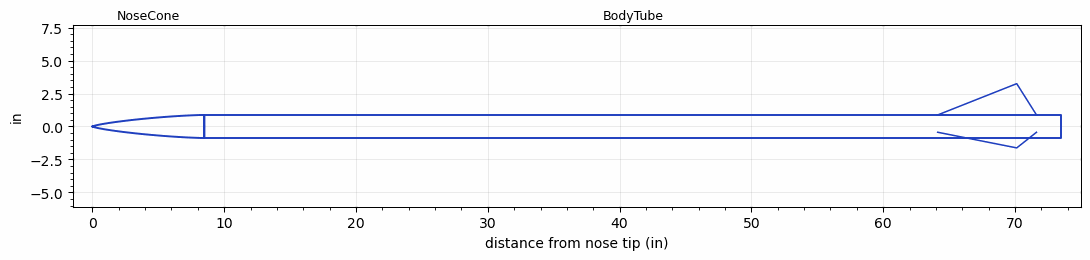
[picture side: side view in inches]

<RASAeroDocument>
 <FileVersion>2</FileVersion>
 <RocketDesign>
  <NoseCone>
   <Length>8.5</Length>
   <Diameter>1.75</Diameter>
   <Shape>Von Karman Ogive</Shape>
   <Location>0</Location>
  </NoseCone>
  <BodyTube>
   <Length>65</Length>
   <Diameter>1.75</Diameter>
   <RailGuideDiameter>0.375</RailGuideDiameter>
   <RailGuideHeight>0.3438</RailGuideHeight>
   <Location>8.5</Location>
   <Fin>
    <Count>3</Count>
    <Chord>7.5</Chord>
    <Span>2.375</Span>
    <SweepDistance>6</SweepDistance>
    <TipChord>0</TipChord>
    <Thickness>0.125</Thickness>
    <Location>9.370003</Location>
    <AirfoilSection>Rounded</AirfoilSection>
   </Fin>
  </BodyTube>
  <Surface>Smooth (Zero Roughness)</Surface>
  <ModifiedBarrowman>False</ModifiedBarrowman>
  <Turbulence>False</Turbulence>
  <UseBooster1>False</UseBooster1>
  <UseBooster2>False</UseBooster2>
  <Comments>Raven - Dave Rose
LDRS-26
Jean Dry Lake

Barometric Altimeter
Altitude = 8815 ft

RASAero II Prediction = 9332 ft
Error = 5.87%
</Comments>
 </RocketDesign>
 <LaunchSite>
  <Altitude>2750</Altitude>
  <Pressure>0</Pressure>
  <RodAngle>0</RodAngle>
  <RodLength>10</RodLength>
  <Temperature>100</Temperature>
  <WindSpeed>0</WindSpeed>
 </LaunchSite>
 <Recovery>
  <Altitude1>1000</Altitude1>
  <Altitude2>1000</Altitude2>
  <DeviceType1>None</DeviceType1>
  <DeviceType2>None</DeviceType2>
  <Event1>False</Event1>
  <Event2>False</Event2>
  <Size1>1</Size1>
  <Size2>1</Size2>
  <EventType1>None</EventType1>
  <EventType2>None</EventType2>
  <CD1>1.33</CD1>
  <CD2>1.33</CD2>
 </Recovery>
 <SimulationList>
  <Simulation>
   <SustainerEngine>J570W  (AT)</SustainerEngine>
   <SustainerLaunchWt>5.44</SustainerLaunchWt>
   <SustainerCG>54.9</SustainerCG>
   <SustainerIgnitionDelay>0</SustainerIgnitionDelay>
   <Booster1SeparationDelay>0</Booster1SeparationDelay>
   <Booster1IgnitionDelay>0</Booster1IgnitionDelay>
   <IncludeBooster1>False</IncludeBooster1>
   <Booster2Delay>0</Booster2Delay>
   <IncludeBooster2>False</IncludeBooster2>
   <TimetoApogee>20.85038</TimetoApogee>
   <MaxAltitude>9331.979</MaxAltitude>
   <MaxVelocity>1243.414</MaxVelocity>
  </Simulation>
 </SimulationList>
</RASAeroDocument>
